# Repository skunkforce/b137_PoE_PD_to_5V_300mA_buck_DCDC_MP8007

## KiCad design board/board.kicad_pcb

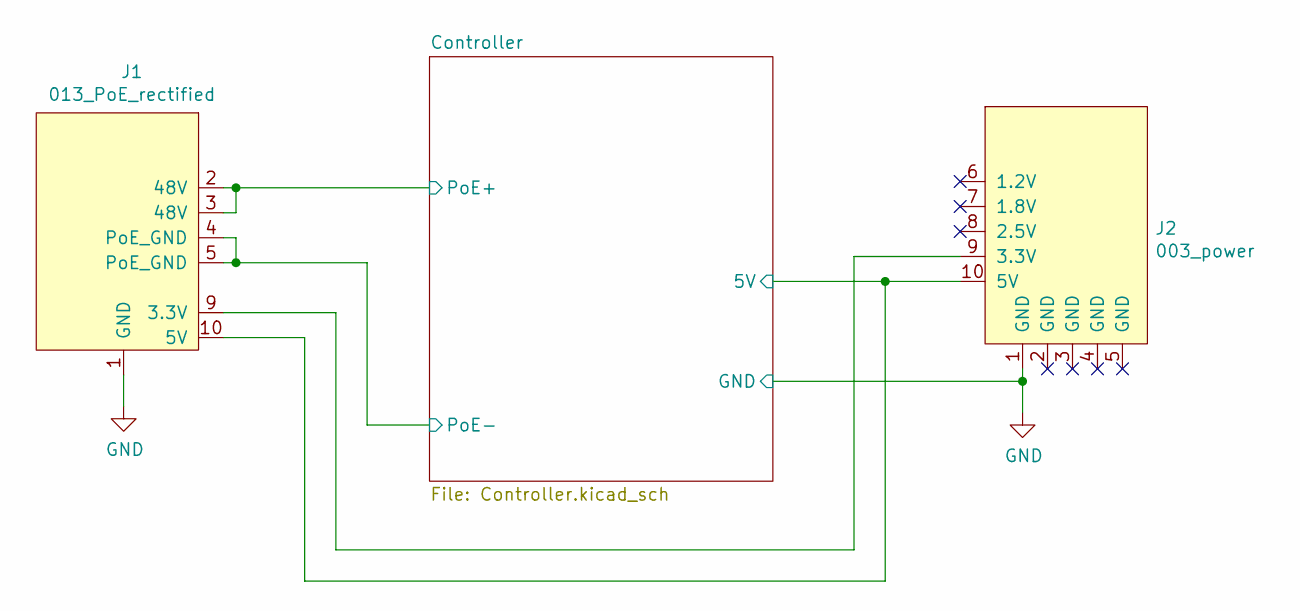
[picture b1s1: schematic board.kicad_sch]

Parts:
J1: 013_PoE_rectified; on_edge_2x05_device
J2: 003_power; on_edge_2x05_host

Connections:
/Controller/5V: J1.2 (48V), J1.3 (48V), J1.10 (5V), J2.10 (5V); also elsewhere on the board
/Controller/PoE-: J1.4 (PoE_GND), J1.5 (PoE_GND); also elsewhere on the board
GND: J1.1 (GND), J2.1 (GND); also elsewhere on the board
unnamed: J1.9 (3.3V), J2.9 (3.3V)

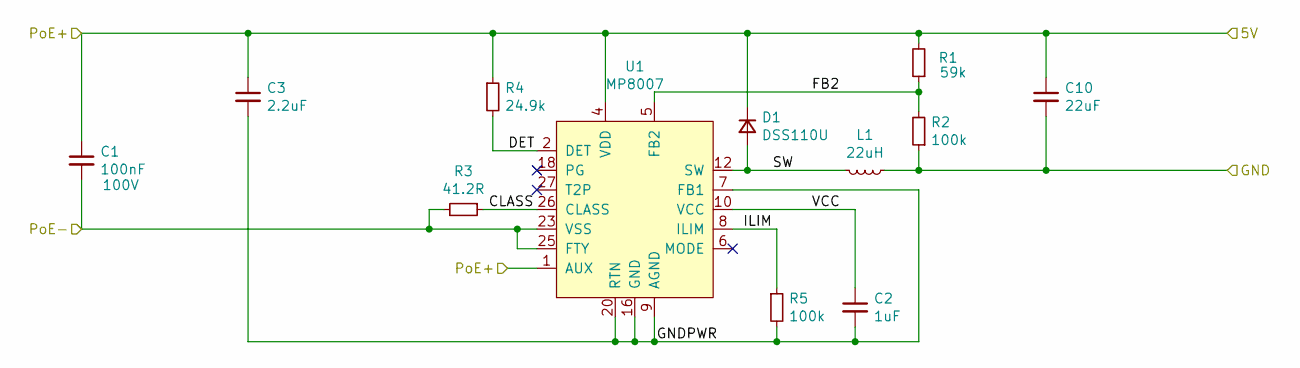
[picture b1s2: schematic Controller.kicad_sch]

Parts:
C1: 100nF; C_0603_1608Metric; Voltage 100V
C2: 1uF; C_0402_1005Metric
C3: 2.2uF; C_1206_3216Metric
C10: 22uF; C_0603_1608Metric
D1: DSS110U; D_SOD-323F; MPN DSS110U
L1: 22uH; L_Taiyo-Yuden_NR-30xx; MPN HPC 3015TF-220M; Digi-Key_PN 4816-HPC3015TF-220MCT-ND
R1: 59k; R_0402_1005Metric
R2, R5: 100k; R_0402_1005Metric
R3: 41.2R; R_0402_1005Metric
R4: 24.9k; R_0402_1005Metric
U1: MP8007; QFN-28-1EP_4x5mm_P0.5mm_EP2.65x3.65mm_ThermalVias

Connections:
/Controller/5V: C1.1, C3.1, C10.1, D1.1 (K), R1.2, R4.1, U1.1 (AUX), U1.4 (VDD); also elsewhere on the board
/Controller/CLASS: R3.1, U1.26 (CLASS)
/Controller/DET: R4.2, U1.2 (DET)
/Controller/FB2: R1.1, R2.2, U1.5 (FB2)
/Controller/GNDPWR: C2.2, C3.2, R5.2, U1.7 (FB1), U1.9 (AGND), U1.14 (NC), U1.15 (NC), U1.16 (GND), U1.17, U1.19 (NC), U1.20 (RTN), U1.21, U1.22 (NC), U1.29 (GND)
/Controller/ILIM: R5.1, U1.8 (ILIM)
/Controller/PoE-: C1.2, R3.2, U1.23 (VSS), U1.24, U1.25 (FTY); also elsewhere on the board
/Controller/SW: D1.2 (A), L1.2, U1.12 (SW), U1.13
/Controller/VCC: C2.1, U1.10 (VCC)
GND: C10.2, L1.1, R2.1; also elsewhere on the board

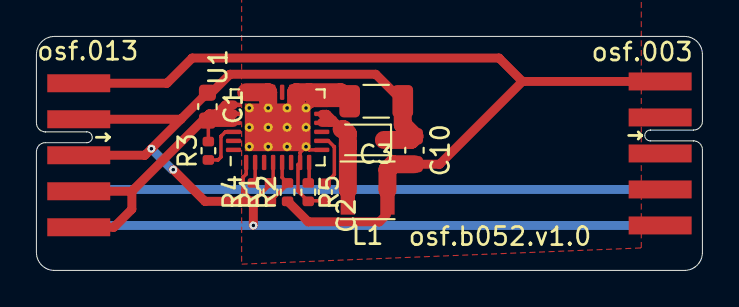
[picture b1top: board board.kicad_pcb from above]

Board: 2 copper layers, 37.0 x 13.0 mm, 14 parts (0 on the bottom side), 11 nets.

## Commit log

2023-06-03 initial
